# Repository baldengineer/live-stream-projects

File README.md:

# live stream projects
 Bald Engineer's Livestream projects

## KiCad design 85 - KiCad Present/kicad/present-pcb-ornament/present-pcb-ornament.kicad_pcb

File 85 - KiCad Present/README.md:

## KiCad Present / Ornament

KiCad stuff.

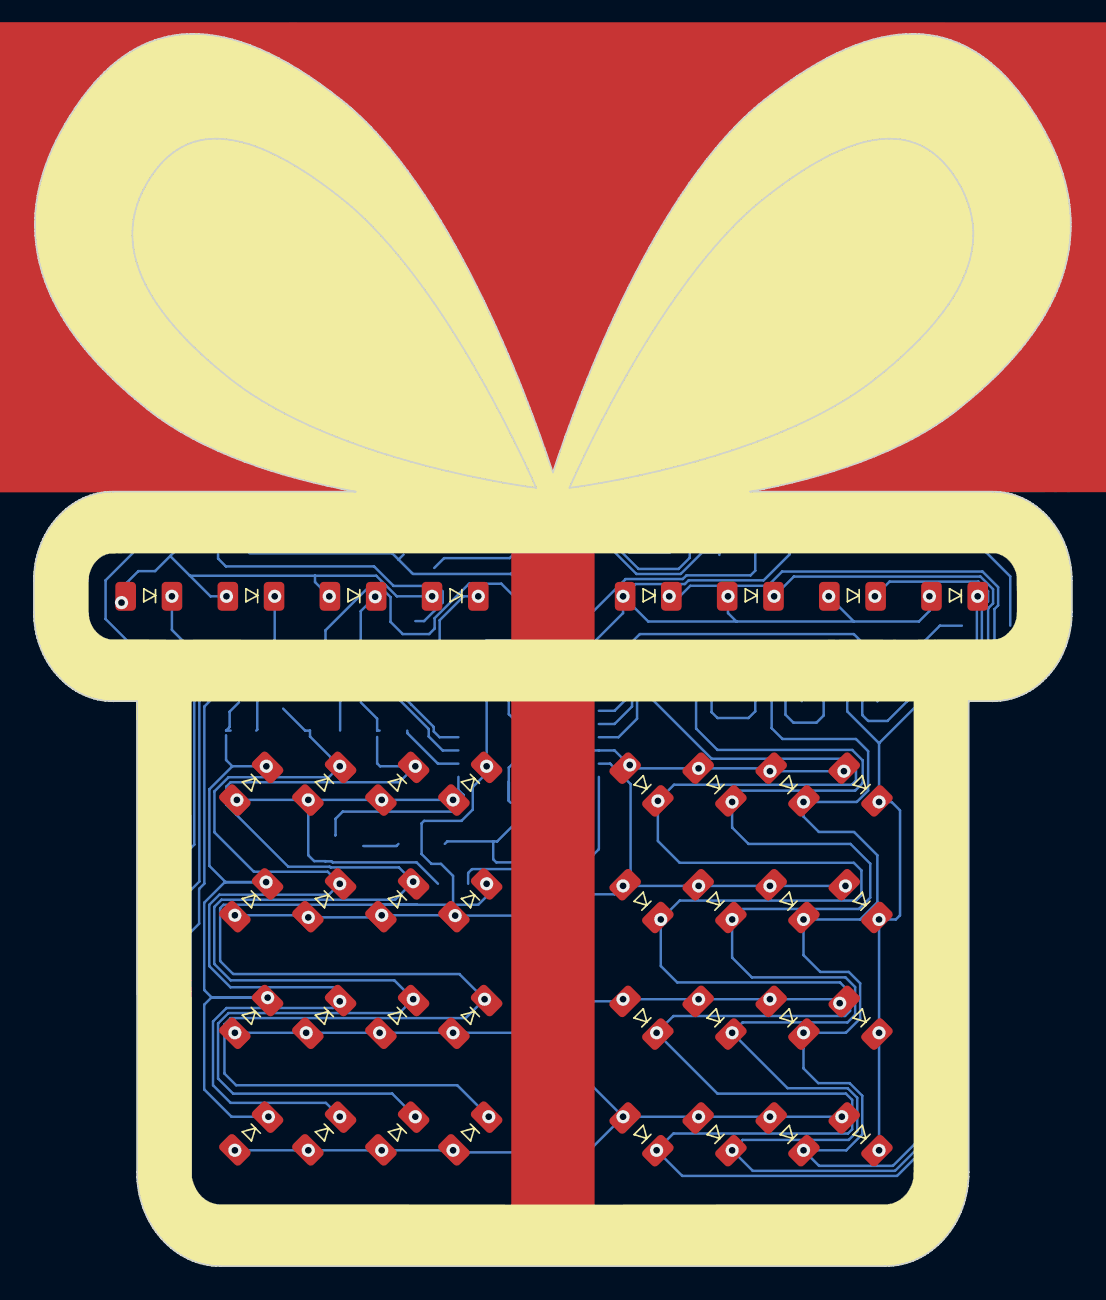
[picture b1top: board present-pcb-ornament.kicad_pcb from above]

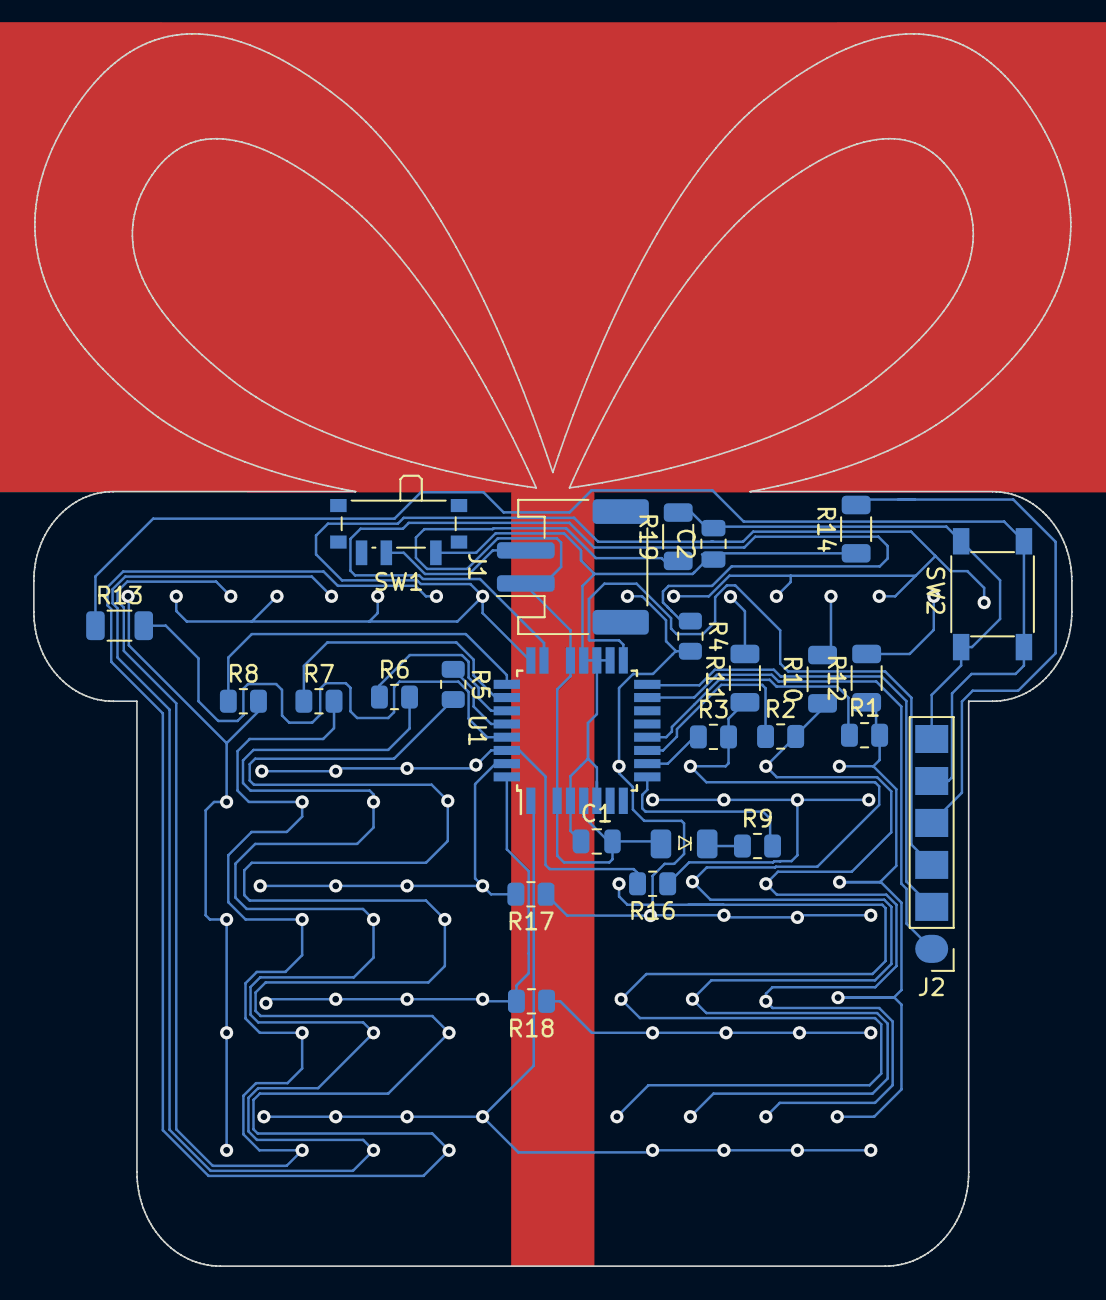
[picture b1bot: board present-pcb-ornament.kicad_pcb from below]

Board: 2 copper layers, 62.8 x 74.6 mm, 67 parts (26 on the bottom side), 30 nets.

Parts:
C1, C2: 10u; C_0805_2012Metric
D1, D34, D35, D36, D37, D38, D39, D40, D41: RED; LED_1206_3216Metric-NoSilk
D2, D3, D4, D5, D6, D7, D8, D9, D10, D11, D12, D13, D14, D15, D16, D17, D18, D19, D20, D21, D22, D23, D24, D25, D26, D27, D28, D29, D30, D31, D32: GRN; LED_1206_3216Metric-NoSilk
D33: Batt; LED_1206_3216Metric-NoSilk
H1: PCB; inky escaped
J1: Batt; JST_PH_S2B-PH-SM4-TB_1x02-1MP_P2.00mm_Horizontal
J2: ISP; PinHeader_1x06_P2.54mm_SMD_Field
R1, R2, R3, R4, R5, R6, R7, R8: R_0805; R_0805_2012Metric
R9: 1K; R_0805_2012Metric
R10, R11, R12, R13, R14, R19: 0; R_1206_3216Metric
R16, R17, R18: 0; R_0805_2012Metric
SW1: PWR; SW_SPDT_PCM12-no-mounts
SW2: RESET; SW_Push_CK_PTS525_SM15
U1: ATmega8A-AU; TQFP-32_7x7mm_P0.8mm

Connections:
/MISO: J2.2, U1.16
/MOSI: J2.1, U1.15
/Pin1: R1.1, U1.12
/Pin2: R2.1, U1.11
/Pin3: R3.1, U1.10
/Pin4: R4.1, U1.23
/Pin5: R5.1, U1.28
/Pin6: R6.1, U1.27
/Pin7: R7.1, U1.26
/Pin8: R8.1, U1.25
/Pin9: D34.1, D35.1, D36.1, D37.1, D38.1, D39.1, D40.1, D41.1, U1.24
/Pin10: D1.1, D5.1, D9.1, D13.1, D17.1, D21.1, D25.1, D29.1, R16.1, R16.2, U1.30
/Pin11: D2.1, D6.1, D10.1, D14.1, D18.1, D22.1, D26.1, D30.1, R17.1, R17.2, U1.31
/Pin12: D3.1, D7.1, D11.1, D15.1, D19.1, D23.1, D27.1, D31.1, R18.1, R18.2, U1.32
/Pin13: D4.1, D8.1, D12.1, D16.1, D20.1, D24.1, D28.1, D32.1, U1.1
/Pin17: R9.2, U1.9
/RESET: J2.5, R13.1, R13.2, SW2.2, U1.29
/SCK: J2.3, U1.17
/Vin: J1.2, SW1.2
/nR1: D1.2, D2.2, D3.2, D4.2, D34.2, R1.2, R12.1, R12.2
/nR2: D5.2, D6.2, D7.2, D8.2, D35.2, R2.2, R10.1, R10.2
/nR3: D9.2, D10.2, D11.2, D12.2, D36.2, R3.2, R11.1, R11.2
/nR4: D13.2, D14.2, D15.2, D16.2, D37.2, R4.2
/nR5: D17.2, D18.2, D19.2, D20.2, D38.2, R5.2
/nR6: D21.2, D22.2, D23.2, D24.2, D39.2, R6.2
/nR7: D25.2, D26.2, D27.2, D28.2, D40.2, R7.2
/nR8: D29.2, D30.2, D31.2, D32.2, D41.2, R8.2
GND: C1.2, C2.2, D33.1, J1.1, J2.6, R19.1, R19.2, SW2.1, U1.3, U1.5, U1.21
unnamed: D33.2, R9.1
VDD: C1.1, C2.1, J2.4, R14.1, R14.2, SW1.1, U1.4, U1.6, U1.18, U1.19, U1.20

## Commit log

2020-11-29 initial create
2020-12-05 added topic 55
2020-12-05 Update README.md
    minor fix
2020-12-05 notes update
2020-12-05 added image
2020-12-05 added sams link
2020-12-05 added after stream notes
2020-12-06 What the 232 stream notes
2020-12-10 initial 3d modeling notes
2020-12-15 created 555 stream notes
2021-01-02 measured da caps
2021-01-02 added google sheets link
2021-01-02 grouped capacitor "table"
2021-01-03 found all dem caps
2021-01-09 inserting caps stream
2021-01-10 Jan 10 stream notes added URL
2021-01-14 Catalog caps for IIc
2021-01-17 2020-1-17 Stream
2021-01-31 notes when looking at composite mod
2021-01-31 created #59
2021-01-31 adding png for easy access
2021-01-31 oops
2021-01-31 formatting
2021-01-31 more formatting
2021-02-03 2021-01-31 Stream Notes
2021-02-04 02-03 making measurements
    measured TTL, S, LS, HC, HCT, AHCT
2021-02-05 adding 02-05 notes
2021-02-05 pictures
2021-02-07 created topic #60
2021-02-08 2/7 stream notes added
2021-02-11 add link to design files for 60
2021-02-13 create 61-Nomad Notes
2021-02-15 sunday stream update
2021-03-13 added nomad cap link
2021-03-13 post stream notes
2021-03-14 created 62
2021-03-14 added link to 62
2021-03-20 added 63
2021-03-21 added 64, finished 63
2021-03-22 images during stream and updated notes
2021-03-22 testing new git tool
2021-03-24 added initial 65 notes
2021-03-26 Stream prep
2021-03-26 added Commodore DOS commands for reference in the stream
2021-03-26 added shortcuts from wikipedia
2021-03-27 finished stream - initial decoding of IEC bus
2021-03-27 post stream
2021-03-28 added missing bus commands
2021-03-28 re-arranged code
2021-04-04 added 68 for VL53L0X sensor. also fixed file name on #57 (compostie mod)
2021-04-11 added #70
2021-04-12 typo
2021-04-14 added 71
2021-04-18 updates pre-4/18 stream
2021-04-19 added link to phototransistor
2021-04-19 Post 4/18 notes. It was a good stream.
2021-04-21 added link for audio
2021-04-21 adding sample sound effect
2021-04-21 post-stream notes. qualified success.
2021-04-24 new sound effect
2021-04-29 updated notes
2021-05-09 closed 72 and added 73
2021-05-14 initial create for 73
2021-05-17 post stream update
2021-05-26 added 75
2021-05-27 post-stream notes for #75.
2021-05-28 added #76
2021-06-18 added 78
2021-06-23 added notes page for 79
2021-07-25 iie keyboard emulator
2021-08-04 resources added
2021-08-06 it booted
2021-08-07 changed circuitpython scripts to .py
2021-08-23 Create FUNDING.yml
    added sponsor button
2021-09-01 pico de boardo
2021-09-08 added links to design files and link to brached prototyping pcb for stream 80/8
2021-09-08 rp2040 notes
2021-09-12 re-conning topic 41 from feb 2021, in anticipation of Sep 2021 stream.
2021-09-15 pins outs and notes for reflow programming (41)
2021-09-25 after stream updates
2021-10-11 post 10/10 stream update
2021-10-15 added VC notes
2021-11-25 create notes for 85
2021-11-26 initial project submit
2021-11-26 pre-stream files
2021-11-28 new approach: atmega8 design
2021-11-29 Stupid GND is Stupid
2021-11-29 Got GND. 9 remaining routes are the 0 ohm shorts.
2021-12-16 moved to its own project.
2022-02-07 added joystick/paddle/555 notes
2022-02-07 one moar note! about 555 circuit
2022-02-11 oapl, reset, and joystick notes
2022-02-19 tracing software crashes with LA notes
2022-07-30 Mega IIe Rev3b notes
2022-08-07 added 45 notes
2022-09-30 Game Gear Surface Mount Recap Notes
2022-10-23 adding 92 and 93
2022-11-04 update after finishing recap
2022-12-11 Added proj 96
2022-12-12 added link for 96
